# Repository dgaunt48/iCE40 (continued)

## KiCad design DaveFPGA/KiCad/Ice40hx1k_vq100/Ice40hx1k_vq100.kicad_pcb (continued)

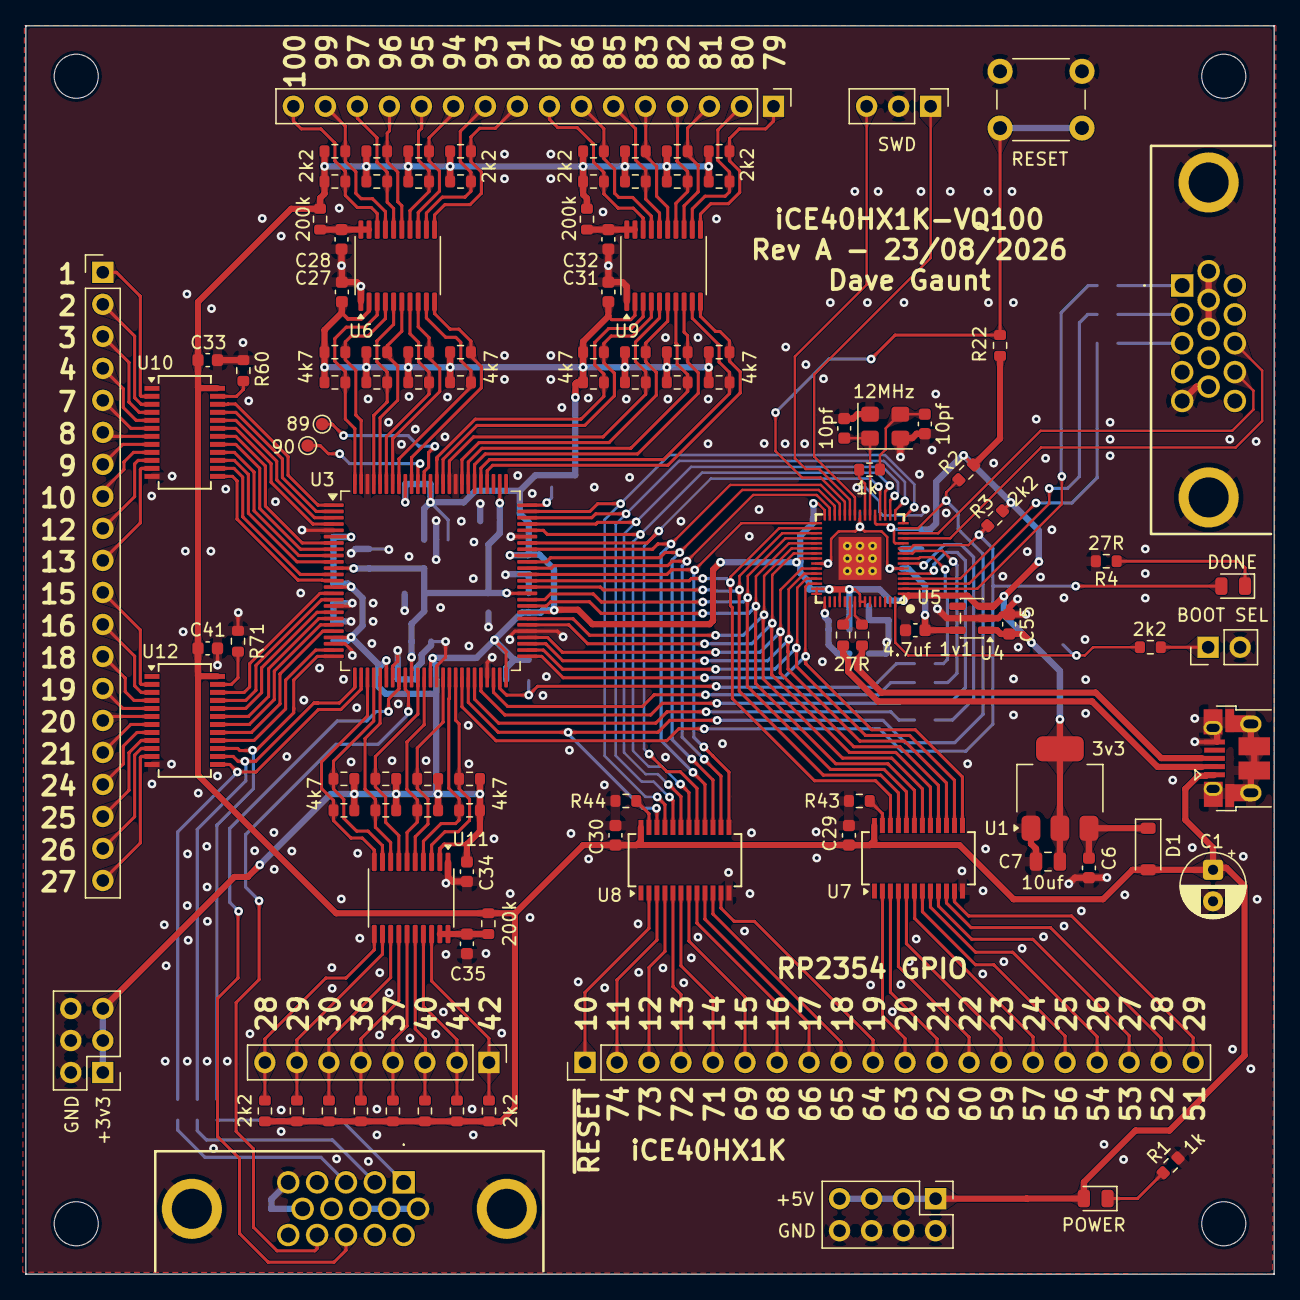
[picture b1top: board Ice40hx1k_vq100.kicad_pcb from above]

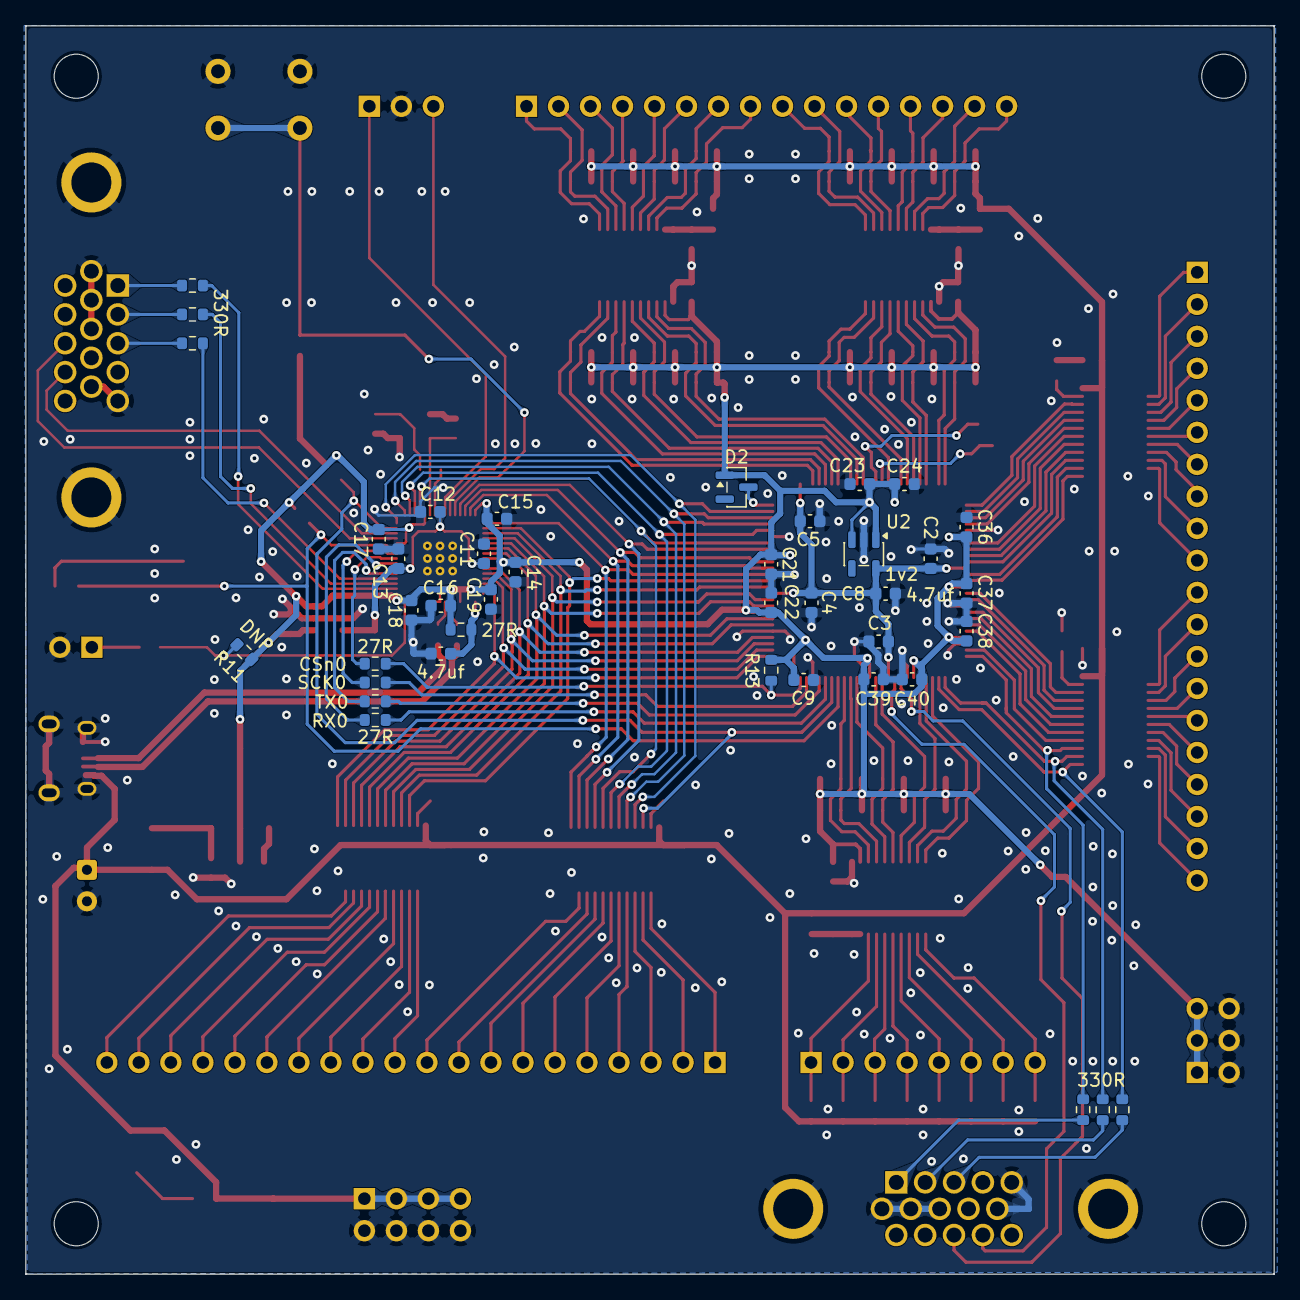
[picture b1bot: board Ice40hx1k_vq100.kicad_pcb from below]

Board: 2 copper layers, 99.1 x 99.1 mm, 154 parts (40 on the bottom side), 181 nets.

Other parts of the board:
C55: 100nf; C_0603_1608Metric

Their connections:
+3V3: C55.2; also elsewhere on the board
GND: C55.1; also elsewhere on the board
